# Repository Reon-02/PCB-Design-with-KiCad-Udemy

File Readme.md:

# PCB Design with KiCad — Udemy Course

<p align="center">
  A collection of PCB designs completed while following the
  <strong>PCB Design with KiCad - Updated for KiCad 9</strong> Udemy course.
</p>

---

## About

This repository contains the PCB designs, schematics, BOMs, manufacturing files, and supporting documentation created while completing the course.

The projects were developed as part of my practical learning process to gain hands-on experience with **schematic capture, component selection, PCB layout, routing, design verification, and preparation of PCB manufacturing files**.

The repository contains projects ranging from a simple LED circuit to power supply designs and a microcontroller-based data logger.

---

## Course

### PCB Design with KiCad - Updated for KiCad 9

**Platform:** Udemy

[View Course](https://www.udemy.com/share/105YR03@hdEVWNpVydDwXK-DHMVmjIG6j6jP2o1doZVhvYaCLZwN9b4QRBgg-SJO-xgzQPG_Kw==/)

---

## Projects

| No. | Project | Description |
|:---:|---|---|
| 01 | [LED Torch](./01_LED_Torch/) | Compact LED torch PCB |
| 02 | [Breadboard Power Supply](./02_Breadboard_Power_Supply/) | 5 V / 3.3 V regulated power supply |
| 03 | [Solar Power Supply](./03_Solar_Power_Supply/) | Solar-powered boost converter PCB |
| 04 | [MCU Data Logger](./04_MCU_Datalogger/) | ATmega328P-based data logger PCB |
---

## Skills Practiced

### PCB Design

- Schematic Capture
- Component Selection
- Footprint Assignment
- PCB Layout
- PCB Routing
- Ground Plane Creation
- Design Rule Checking (DRC)

### Manufacturing & Documentation

- Interactive BOM Generation
- Datasheet Reference
- Gerber Generation
- Gerber Verification
- PCB 3D Visualization
- Manufacturing File Preparation

### Version Control

- Git
- GitHub
- Repository Organization

---

## Tools Used

---

## Repository Structure

```text
PCB Design with KiCad-Udemy/
│
├── README.md
│
├── 01_LED_Torch/
│   ├── README.md
│   ├── KiCad/
│   ├── BOM/
│   ├── Gerbers/
│   └── Images/
│
├── 02_Breadboard_Power_Supply/
│   ├── README.md
│   ├── BOM/
│   ├── Datasheets/
│   ├── Gerbers/
│   ├── Images/
│   └── KiCad/
│
├── 03_Solar_Power_Supply/
│   ├── README.md
│   ├── BOM/
│   ├── Datasheets/
│   ├── Gerbers/
│   └── Images/
│
└── 04_MCU_Datalogger/
    ├── README.md
    ├── BOM/
    ├── Datasheets/
    ├── Gerbers/
    ├── Images/
    ├── Kicad_2layer/
    └── Kicad_4layer/

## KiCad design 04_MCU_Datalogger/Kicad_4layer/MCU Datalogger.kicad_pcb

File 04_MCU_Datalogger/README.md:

# MCU Data Logger

A microcontroller-based data logger PCB designed using KiCad as part of the **PCB Design with KiCad - Updated for KiCad 9** Udemy course.

The project is built around an **ATmega328P-AU** microcontroller and includes an external real-time clock, EEPROM memory, communication interfaces, programming interface, and external I/O connections. Both **2-layer and 4-layer PCB versions** were designed.

---

## Features

- ATmega328P-AU microcontroller
- DS1337S real-time clock
- External EEPROM memory
- I²C communication
- UART interface
- ISP programming interface
- 2-layer and 4-layer PCB versions
- Interactive HTML BOM
- Gerber generation and verification

---

## Working

The ATmega328P-AU acts as the main controller of the data logger. It communicates with the DS1337S real-time clock and external EEPROM through the I²C interface.

The real-time clock provides accurate time information, while the external EEPROM provides non-volatile memory for storing data.

The PCB also provides UART connectivity for serial communication and an ISP interface for programming the ATmega328P-AU. External connectors expose power, communication signals, and GPIO connections for interfacing with other circuits or modules.

The microcontroller operates using an external crystal oscillator, while the DS1337S uses a dedicated 32.768 kHz crystal for timekeeping.

---

## Schematic

The complete MCU Data Logger circuit was designed using KiCad.

---

## Layout Design

Two PCB implementations were developed for the project.

### 2-Layer PCB — Without Ground Zone

### 2-Layer PCB — With Ground Zone

### 4-Layer PCB — Without Ground Zone

### 4-Layer PCB — With Ground Zone

---

## 3D Visualization

### Front View

### Back View

---

## Components

| Reference | Component | Purpose |
|---|---|---|
| U4 | ATmega328P-AU | Main microcontroller |
| U3 | DS1337S | Real-time clock |
| U1, U2 | 24LC1025 | External EEPROM memory |
| Y1 | 32.768 kHz Crystal | RTC clock source |
| Y2 | 16 MHz Crystal | MCU clock source |
| D1 | LED | Power indication |
| J4 | ISP Connector | MCU programming |
| J1–J3 | External Connectors | Power, communication and I/O |
| H1–H4 | Mounting Holes | PCB mounting |

---

## Interactive BOM

The Interactive BOM provides component references, values, footprints, quantities, and interactive PCB component highlighting.

**[View Interactive BOM](https://reon-02.github.io/PCB-Design-with-KiCad-Udemy/04_MCU_Datalogger/BOM/MCU_Datalogger_ibom.html)**

---

## Design Verification

The PCB designs were checked using KiCad Design Rule Check (DRC), and the generated Gerber files were verified using the KiCad Gerber Viewer.

### 2-Layer Gerber Verification

### 4-Layer Gerber Verification

---

## Manufacturing Files

The project includes the generated Gerber and drill files required for PCB manufacturing.

The Gerber files include:

- Copper layers
- Solder mask layers
- Silkscreen layers
- Paste layers
- Edge cuts
- Drill files
- Gerber job file

---

## Datasheets

The relevant component datasheets used during the design are included in the `Datasheets` folder.

- [21941](./Datasheets/21941.pdf)
- [ATmega328P-AU Datasheet](./Datasheets/ATMEGA328PAU_Microchip_Technology.pdf)
- [DS1337S Datasheet](./Datasheets/DS1337S_Maxim_Integrated_Products.pdf)

---

## KiCad Project Files

The KiCad project files for both PCB versions are included in the repository:

- `Kicad_2layer/` — 2-layer PCB design
- `Kicad_4layer/` — 4-layer PCB design

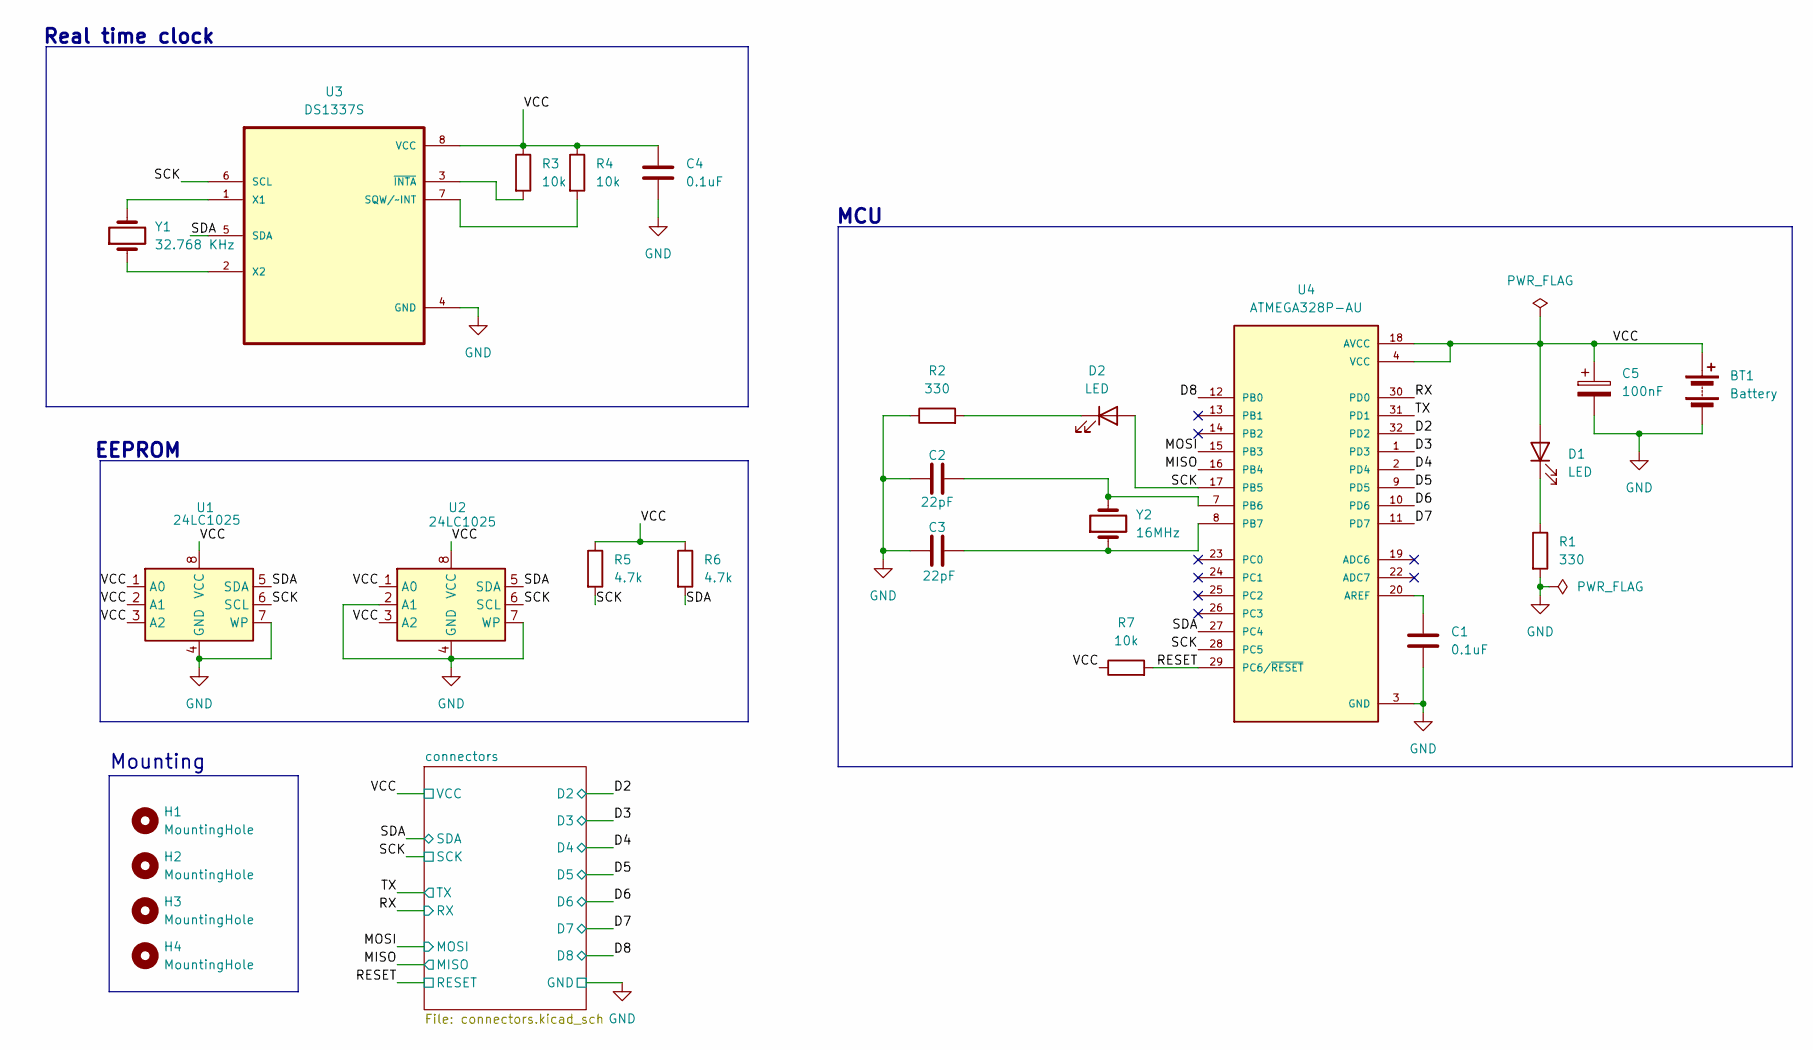
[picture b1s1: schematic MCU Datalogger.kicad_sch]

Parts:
BT1: Battery; PinHeader_1x02_P2.54mm_Vertical
C1, C4: 0.1uF; C_0805_2012Metric
C2, C3: 22pF; C_0805_2012Metric
C5: 100nF; C_0805_2012Metric
D1, D2: LED; LED_0805_2012Metric
H1, H2, H3, H4: MountingHole; MountingHole_2.1mm
R1, R2: 330; R_0805_2012Metric
R3, R4, R7: 10k; R_0805_2012Metric
R5, R6: 4.7k; R_0805_2012Metric
U1, U2: 24LC1025; SOIC-8_5.3x5.3mm_P1.27mm
U3: DS1337S; DS1337S+
U4: ATMEGA328P-AU; PARTREV 8271A
Y1: 32.768 KHz; Crystal_SMD_5032-2Pin_5.0x3.2mm_HandSoldering
Y2: 16MHz; Crystal_SMD_5032-2Pin_5.0x3.2mm_HandSoldering

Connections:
/D2: U4.32 (PD2); also elsewhere on the board
/D3: U4.1 (PD3); also elsewhere on the board
/D4: U4.2 (PD4); also elsewhere on the board
/D5: U4.9 (PD5); also elsewhere on the board
/D6: U4.10 (PD6); also elsewhere on the board
/D7: U4.11 (PD7); also elsewhere on the board
/D8: U4.12 (PB0); also elsewhere on the board
/MISO: U4.16 (PB4); also elsewhere on the board
/MOSI: U4.15 (PB3); also elsewhere on the board
/RESET: R7.2, U4.29 (PC6/~RESET); also elsewhere on the board
/RX: U4.30 (PD0); also elsewhere on the board
/SCK: D2.2 (A), R5.2, U1.6 (SCL), U2.6 (SCL), U3.6 (SCL), U4.17 (PB5), U4.28 (PC5); also elsewhere on the board
/SDA: R6.2, U1.5 (SDA), U2.5 (SDA), U3.5 (SDA), U4.27 (PC4); also elsewhere on the board
/TX: U4.31 (PD1); also elsewhere on the board
GND: BT1.2 (-), C1.1, C2.1, C3.1, C4.2, C5.2, R1.2, R2.1, U1.4 (GND), U1.7 (WP), U2.2 (A1), U2.4 (GND), U2.7 (WP), U3.4 (GND), U4.3 (GND), U4.5 (GND), U4.21 (GND); also elsewhere on the board
unnamed: D1.1 (K), R1.1
unnamed: D2.1 (K), R2.2
unnamed: R4.2, U3.7 (SQW/~INT)
unnamed: U3.1 (X1), Y1.2
unnamed: U3.2 (X2), Y1.1
unnamed: R3.2, U3.3 (~INTA)
unnamed: C1.2, U4.20 (AREF)
unnamed: C2.2, U4.7 (PB6), Y2.2
unnamed: C3.2, U4.8 (PB7), Y2.1
VCC: BT1.1 (+), C4.1, C5.1, D1.2 (A), R3.1, R4.1, R5.1, R6.1, R7.1, U1.1 (A0), U1.2 (A1), U1.3 (A2), U1.8 (VCC), U2.1 (A0), U2.3 (A2), U2.8 (VCC), U3.8 (VCC), U4.4 (VCC), U4.6 (VCC), U4.18 (AVCC); also elsewhere on the board

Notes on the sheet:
MCU
EEPROM
Mounting
Real time clock

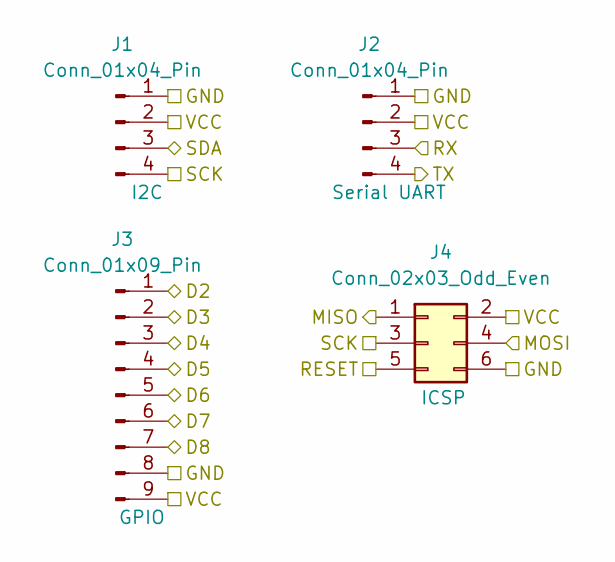
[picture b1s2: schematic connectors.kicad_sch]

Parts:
J1, J2: Conn_01x04_Pin; PinHeader_1x04_P2.54mm_Vertical
J3: Conn_01x09_Pin; PinHeader_1x09_P2.54mm_Vertical
J4: Conn_02x03_Odd_Even; PinHeader_2x03_P2.54mm_Vertical

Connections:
/D2: J3.1; also elsewhere on the board
/D3: J3.2; also elsewhere on the board
/D4: J3.3; also elsewhere on the board
/D5: J3.4; also elsewhere on the board
/D6: J3.5; also elsewhere on the board
/D7: J3.6; also elsewhere on the board
/D8: J3.7; also elsewhere on the board
/MISO: J4.1; also elsewhere on the board
/MOSI: J4.4; also elsewhere on the board
/RESET: J4.5; also elsewhere on the board
/RX: J2.3; also elsewhere on the board
/SCK: J1.4, J4.3; also elsewhere on the board
/SDA: J1.3; also elsewhere on the board
/TX: J2.4; also elsewhere on the board
GND: J1.1, J2.1, J3.8, J4.6; also elsewhere on the board
VCC: J1.2, J2.2, J3.9, J4.2; also elsewhere on the board

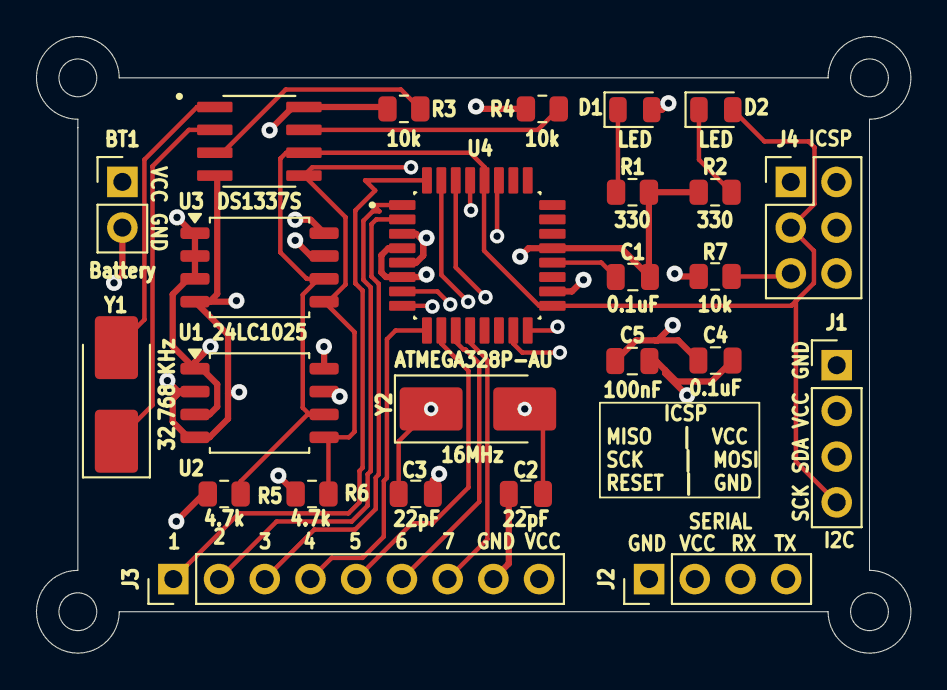
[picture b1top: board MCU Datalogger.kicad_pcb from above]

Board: 4 copper layers, 48.6 x 34.3 mm, 29 parts (0 on the bottom side), 25 nets.

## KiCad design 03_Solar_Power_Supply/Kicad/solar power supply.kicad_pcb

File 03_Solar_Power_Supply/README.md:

# Solar Power Supply

## Overview

This project is part of the **Solar Power Supply** section of the **PCB Design with KiCad - Updated for KiCad 9** Udemy course.

The circuit is designed to accept power from a solar source and provide a regulated output using a boost converter based on the **AP3015AKTR-G1**.

The design includes input protection, battery connection, power switching, boost conversion, filtering, and output voltage feedback.

---

## Features

- Solar power input
- Battery connection
- Reverse-polarity protection
- AP3015AKTR-G1 boost converter
- Inductor-based DC-DC conversion
- Output voltage feedback

---

## Working Principle

The solar power supply is designed to accept power from a solar source or battery and use a boost converter to generate the required output voltage.

### Solar Input

The solar input is connected through the input connector. An SS14 Schottky diode is used at the input to provide reverse-current protection and prevent current from flowing back toward the solar source.

### Battery and Power Switching

A battery can also be connected to the circuit. The solar and battery power paths are connected to the power switching section, where the 2N7002 MOSFET and associated resistors control the connection of the available input power to the boost converter.

### Boost Conversion

The AP3015AKTR-G1 boost converter performs the main DC-DC voltage conversion. The converter uses an external 10 µH inductor and switching circuitry to transfer energy from the input to the output and generate a higher voltage.

### Output Filtering

An SS14 Schottky diode is used in the boost converter output path. The output capacitors filter the converted voltage and reduce voltage ripple, providing a smoother DC output.

### Output Voltage Regulation

The output voltage is monitored using a resistor feedback network consisting of R1 and R2. The feedback voltage is applied to the FB pin of the AP3015, allowing the converter to adjust its switching operation and maintain the required output voltage.

---

## Schematic

The complete Solar Power Supply circuit was designed using KiCad.

---

## PCB Design

The PCB was designed using KiCad with the components arranged for a compact solar power supply circuit.

### PCB Layout

---

## 3D Visualization

### Front View

### Back View

---

## Components

| Reference | Component | Value / Part |
|---|---|---|
| U1 | Boost Converter | AP3015AKTR-G1 |
| Q1 | N-Channel MOSFET | 2N7002 |
| L1 | Inductor | 10 µH, 680 mA |
| D1 | Schottky Diode | SS14 |
| D2 | Schottky Diode | SS14 |
| R1 | Resistor | 1 MΩ |
| R2 | Resistor | 604 kΩ, 1% |
| R3 | Resistor | 10 kΩ |
| R4 | Resistor | 1 MΩ |
| C1 | Capacitor | 4.7 µF, 50 V, X7R |
| C2 | Capacitor | 22 µF, 10 V, X7R |
| C3 | Capacitor | 10 pF, 50 V, X7R |
| J2 | Connector | Battery Input |
| J4 | Connector | Solar Input |
| J3 | Connector | Power Switch |
| J1 | Connector | Output |

---

## Bill of Materials

An Interactive HTML BOM was generated using **InteractiveHtmlBom**.

[Open Interactive BOM](https://reon-02.github.io/PCB-Design-with-KiCad-Udemy/03_Solar_Power_Supply/BOM/Solar_Power_Supply_ibom.html)

The Interactive BOM provides:

- Component references
- Component values
- Footprints
- Component quantities
- Component locations
- Interactive PCB component highlighting

---

## Design Verification

### Design Rule Check

The PCB was checked using KiCad's **Design Rule Checker (DRC)**.

### Gerber Verification

The generated manufacturing files were opened and inspected using KiCad Gerber Viewer.

### Gerber Viewer with Ground Zone

---

## Manufacturing Files

The `Gerbers/` directory contains the manufacturing outputs generated from KiCad, including:

- Copper layers
- Solder mask layers
- Solder paste layers
- Silkscreen layers
- Board outline
- PTH drill file
- NPTH drill file
- Gerber job file

---

## Datasheets

Datasheets for the main components used in the design are included in the `Datasheets/` directory.

- [AP3015A Datasheet](./Datasheets/AP3015_A.pdf)
- [Abracon ASPI-0630LR-100M-T15 Datasheet](./Datasheets/ASPI-0630LR-100M-T15_Abracon.pdf)
- [2N7002A Datasheet](./Datasheets/NDS7002A-D.PDF)
- [SS14 Datasheet](./Datasheets/SS14_ON.pdf)

---

## KiCad Project Files

The complete KiCad project files are included in the project directory.

```text
solar power supply.kicad_pro
solar power supply.kicad_sch
solar power supply.kicad_pcb

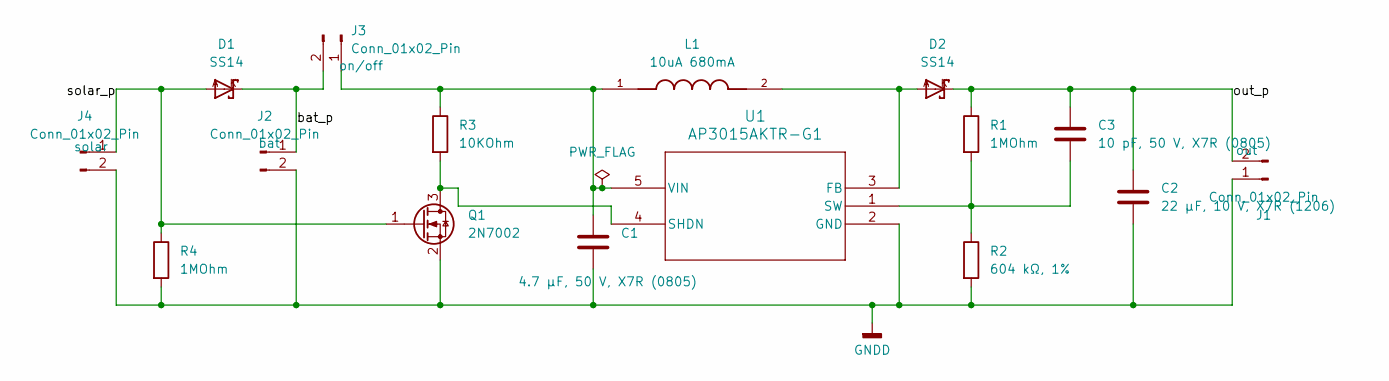
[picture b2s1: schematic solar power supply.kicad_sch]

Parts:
C1: 4.7 μF, 50 V, X7R (0805); C_0805_2012Metric
C2: 22 μF, 10 V, X7R (1206); C_1206_3216Metric
C3: 10 pF, 50 V, X7R (0805); C_0805_2012Metric
D1, D2: SS14
J1, J2, J4: Conn_01x02_Pin; PinHeader_1x02_P2.54mm_Horizontal
J3: Conn_01x02_Pin; SW_DIP_SPSTx01_Slide_9.78x4.72mm_W7.62mm_P2.54mm
L1: 10uA 680mA; IND_ASPI-0630LR-100M-T15; PARTREV B
Q1: 2N7002; SOT-23
R1, R4: 1MOhm; R_0805_2012Metric
R2: 604 kΩ, 1%; R_0805_2012Metric
R3: 10KOhm; R_0805_2012Metric
U1: AP3015AKTR-G1

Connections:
/bat_p: D1.K, J2.1, J3.2
/out_p: C2.1, C3.1, D2.K, J1.2, R1.1
/solar_p: D1.A, J4.1, Q1.1 (G), R4.1
GNDD: C1.2, C2.2, J1.1, J2.2, J4.2, Q1.2 (S), R2.2, R4.2, U1.2 (GND)
unnamed: C1.1, J3.1, L1.1, R3.1, U1.5 (VIN)
unnamed: Q1.3 (D), R3.2, U1.4 (SHDN)
unnamed: D2.A, L1.2, U1.3 (FB)
unnamed: C3.2, R1.2, R2.1, U1.1 (SW)

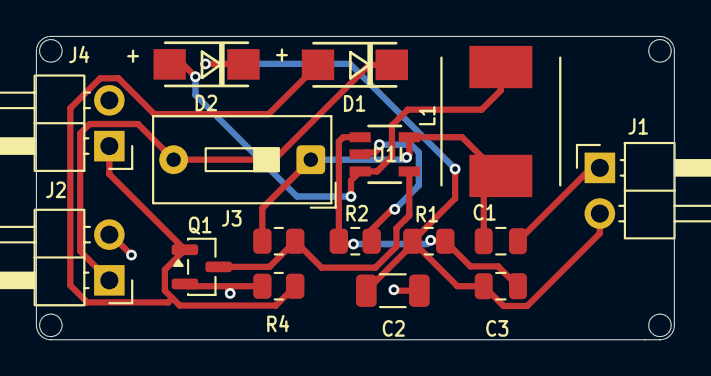
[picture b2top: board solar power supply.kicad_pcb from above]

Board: 2 copper layers, 35.4 x 16.8 mm, 16 parts (0 on the bottom side), 8 nets.

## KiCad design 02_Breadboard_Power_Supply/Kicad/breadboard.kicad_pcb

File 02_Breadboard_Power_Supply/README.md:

# Breadboard Power Supply

## Overview

This project is a breadboard power supply PCB designed as part of the **PCB Design with KiCad - Updated for KiCad 9** Udemy course.

The board accepts a **12 V DC input** and provides regulated **5 V and 3.3 V outputs** for powering breadboard-based electronic circuits.

The PCB includes voltage regulation, a power indicator LED, output selection, breadboard connectors, jumper-wire terminals, and a ground plane.

---

## Features

- 12 V DC input
- Regulated 5 V output using LM7805
- Regulated 3.3 V output using LM317
- Selectable output connectors
---
## Working Principle

The board accepts a 12 V DC input through the barrel jack. The input power is distributed to two voltage regulation sections to generate regulated 5 V and 3.3 V outputs.

### 12 V to 5 V Regulation

The 12 V input is supplied to the LM7805 voltage regulator through the power switch. The LM7805 regulates the input voltage to provide a stable 5 V output. Input and output capacitors are used for filtering and regulator stability.

### 12 V to 3.3 V Regulation

The 12 V input is also supplied to the LM317 adjustable voltage regulator. A resistor network connected to the adjustment circuit sets the regulator output to approximately 3.3 V.

### Power Indicator

An LED with a current-limiting resistor is used as a power indicator. The LED turns on when the board is powered.

### Output connections

The regulated 5 V and 3.3 V outputs are made available through dedicated connectors and screw terminals for connection to a breadboard or external circuit.

---

## Schematic

The complete circuit schematic was designed using KiCad.

---

## PCB Design

The PCB was designed as a compact through-hole board with the regulators, connectors, switch, and other components arranged for breadboard power supply use.

### PCB Layout

### PCB Layout with Ground Zone

---

## 3D Visualization

### Top View

### Alternate Top View

### Side View

### Back View

---

## Components

| Reference | Component | Value / Part |
|---|---|---|
| U1 | 5 V Voltage Regulator | LM7805_TO220 |
| U2 | Adjustable Voltage Regulator | LM317_TO220 |
| S1 | Power Switch | EG1218 |
| D1 | LED | Power Indicator |
| R1 | Resistor | 330 Ω |
| R2 | Resistor | 560 Ω |
| R3 | Resistor | 330 Ω |
| C1 | Capacitor | 10 µF |
| C2 | Capacitor | 0.1 µF |
| C3 | Capacitor | 1 µF |
| J6 | Barrel Jack | DC Power Input |
| J1, J3 | Output Connectors | Breadboard Output |
| J4, J7 | Screw Terminals | Jumper-Wire Output |

---

## Bill of Materials

An Interactive HTML BOM was generated using **InteractiveHtmlBom**.

[View Interactive BOM](https://reon-02.github.io/PCB-Design-with-KiCad-Udemy/02_Breadboard_Power_Supply/BOM/Breadboard_Power_Supply_ibom.html)

The interactive BOM provides:

- Component references
- Component values
- Footprints
- Descriptions
- Datasheet information where available
- Component quantities
- Component locations on the PCB

---

## Design Verification

### Design Rule Check

The PCB was checked using KiCad's Design Rule Checker (DRC).

### Gerber Verification

The generated manufacturing files were opened and inspected using KiCad Gerber Viewer.

### Gerber Viewer with Ground Zone

---

## Manufacturing Files

The `Gerbers/` directory contains the manufacturing outputs generated from KiCad, including:

- Front copper
- Back copper
- Front solder mask
- Back solder mask
- Front solder paste
- Back solder paste
- Front silkscreen
- Back silkscreen
- Board outline
- PTH drill file
- NPTH drill file
- Gerber job file

---

## Datasheets

Datasheets for the main components used in the design are included in the `Datasheets/` directory.

- [EG1218 Switch Datasheet](./Datasheets/EG1218.pdf)
- [LM317 Datasheet](./Datasheets/lm317.pdf)
- [MC7800 Datasheet](./Datasheets/MC7800-D.PDF)

---

## KiCad Project Files

The complete KiCad project files are available in the `KiCad/` directory.

```text
KiCad/
├── breadboard.kicad_pro
├── breadboard.kicad_sch
└── breadboard.kicad_pcb
```

---

## Project Structure

```text
02_Bread_Power_Supply/
│
├── README.md
│
├── KiCad/
│   ├── breadboard.kicad_pro
│   ├── breadboard.kicad_sch
│   └── breadboard.kicad_pcb
│
├── BOM/
│   └── Breadboard_Power_Supply_ibom.html
│
├── Datasheets/
│   ├── EG1218.pdf
│   ├── lm317.pdf
│   └── MC7800-D.PDF
│
├── Gerbers/
│   ├── Gerber files
│   └── Drill files
│
└── Images/
    ├── Schematic.png
    ├── PCB_Layout.png
    ├── PCB_layout_with_zone.png
    ├── 3d_top_view.png
    ├── 3d_top_view1.png
    ├── 3d_side.png
    ├── 3d_back.png
    ├── DRC.png
    ├── Gerber_Viewer.png
    └── Gerber_viewer_zone.png
```

---

## What I Practiced

Through this project, I practiced:

- Schematic capture
- Voltage regulator circuit design
- Component and footprint selection
- Through-hole PCB layout
- PCB routing and ground plane creation
- Design Rule Checking (DRC)
- Interactive BOM generation
- Gerber generation and verification
- Preparing PCB files for manufacturing
---

## Course

This project was completed as part of:

**[PCB Design with KiCad - Updated for KiCad 9](https://www.udemy.com/share/105YR03@hdEVWNpVydDwXK-DHMVmjIG6j6jP2o1doZVhvYaCLZwN9b4QRBgg-SJO-xgzQPG_Kw==/)**

**Platform:** Udemy

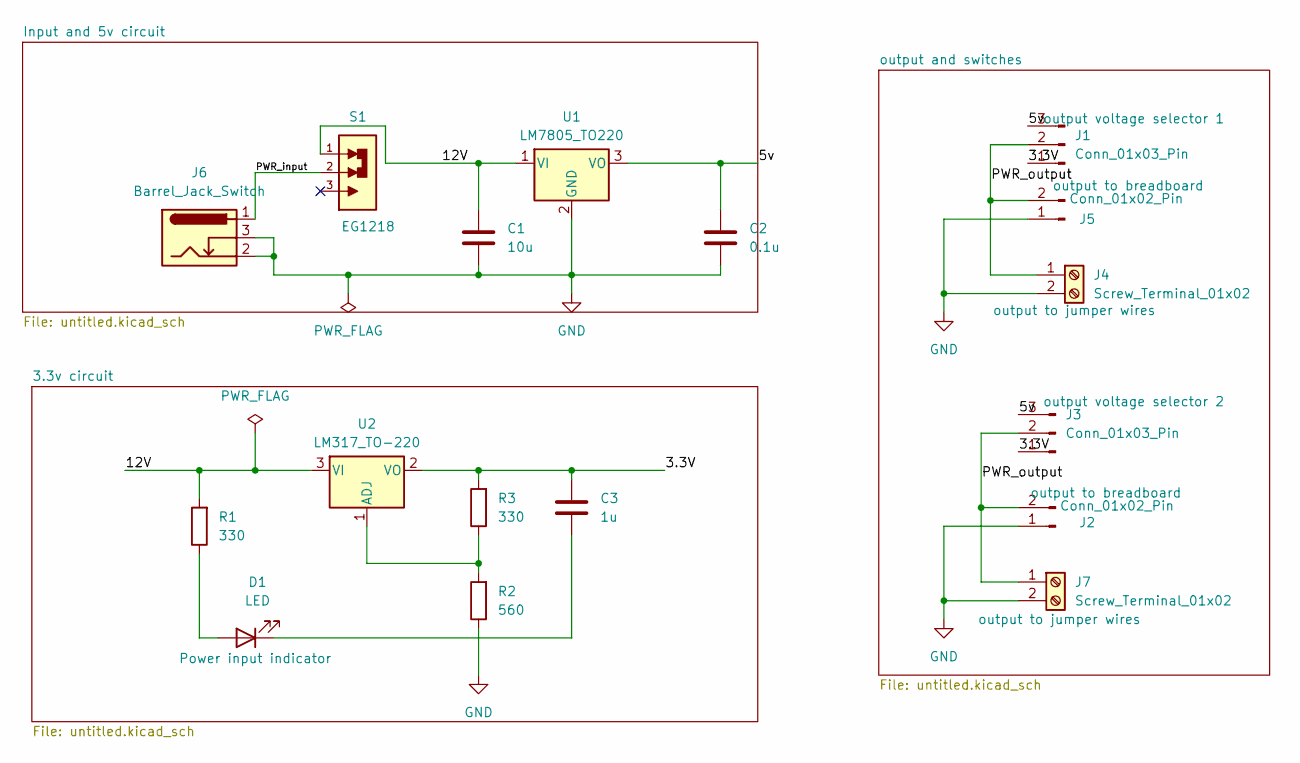
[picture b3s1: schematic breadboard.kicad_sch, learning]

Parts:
C1: 10u; C_Disc_D3.0mm_W1.6mm_P2.50mm
C2: 0.1u; C_Disc_D3.0mm_W1.6mm_P2.50mm
C3: 1u; C_Disc_D3.0mm_W1.6mm_P2.50mm
D1: LED; LED_D5.0mm
J1, J3: Conn_01x03_Pin; PinHeader_1x03_P2.54mm_Vertical
J2, J5: Conn_01x02_Pin; PinHeader_1x02_P2.54mm_Vertical
J4, J7: Screw_Terminal_01x02
J6: Barrel_Jack_Switch; BarrelJack_Horizontal
R1, R3: 330; R_Axial_DIN0204_L3.6mm_D1.6mm_P7.62mm_Horizontal
R2: 560; R_Axial_DIN0204_L3.6mm_D1.6mm_P7.62mm_Horizontal
S1: EG1218; SW_EG1218
U1: LM7805_TO220; TO-220-3_Vertical
U2: LM317_TO-220; TO-220-3_Vertical

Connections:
/3.3V: C3.1, J1.1, J3.1, R3.2, U2.2 (VO)
/5v: C2.1, J1.3, J3.3, U1.3 (VO)
/12V: C1.1, R1.2, S1.1, U1.1 (VI), U2.3 (VI)
/PWR_input: J6.1, S1.2
/PWR_output: J1.2, J2.2, J3.2, J4.1, J5.2, J7.1
GND: C1.2, C2.2, J2.1, J4.2, J5.1, J6.2, J6.3, J7.2, R2.1, U1.2 (GND)
unnamed: D1.2 (A), R1.1
unnamed: C3.2, D1.1 (K)
unnamed: R2.2, R3.1, U2.1 (ADJ)

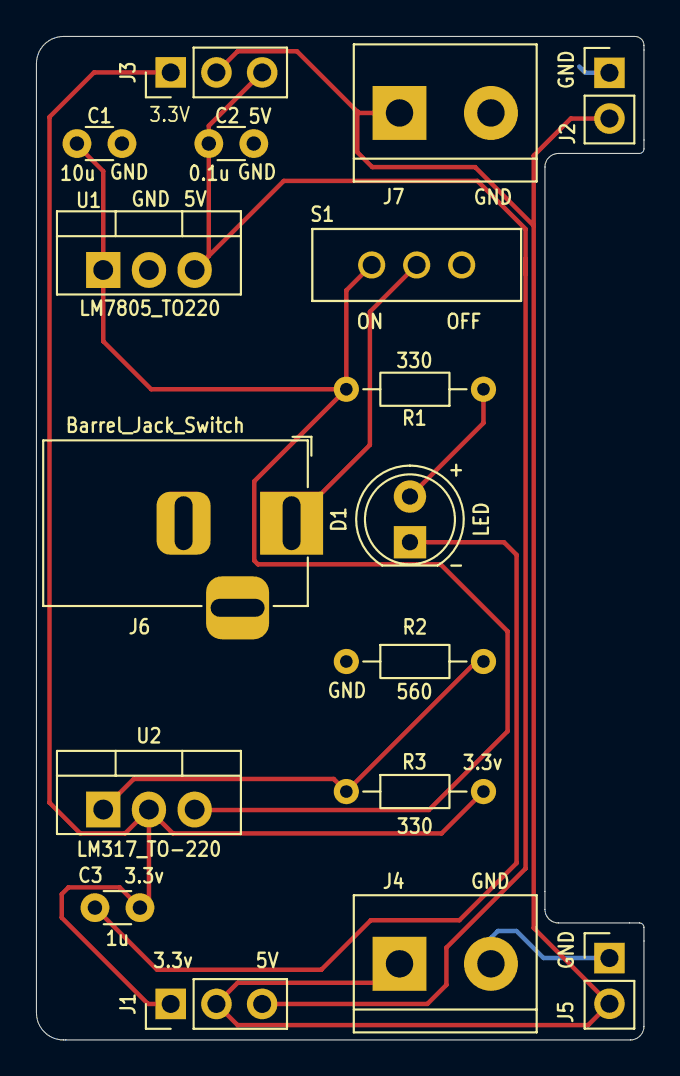
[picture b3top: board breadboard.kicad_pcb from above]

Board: 2 copper layers, 33.8 x 55.8 mm, 17 parts (0 on the bottom side), 9 nets.

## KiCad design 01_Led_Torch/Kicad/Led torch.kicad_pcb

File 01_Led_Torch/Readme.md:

# LED Torch

## Overview

This project is a compact LED torch PCB designed as part of the **PCB Design with KiCad - Updated for KiCad 9** Udemy course.

The circuit uses a single battery cell to power an LED through a current-limiting resistor and an SPST switch.

This project was recreated in KiCad as part of my practical PCB design learning process.

---

## Circuit

The basic circuit consists of:

- Single-cell battery
- SPST ON/OFF switch
- 1 kΩ current-limiting resistor
- 5 mm LED

### Schematic

---

## PCB Design

The PCB was designed as a compact torch-shaped board with an integrated battery holder footprint.

### PCB Layout

### 3D View

#### Front

#### Back

---

## Components

| Reference | Component | Value | Footprint |
|---|---|---|---|
| R1 | Resistor | 1 kΩ | R_Axial_DIN0204_L3.6mm_D1.6mm_P7.62mm_Horizontal |
| D1 | LED | LED | LED_D5.0mm |
| SW1 | SPST Switch | SW_SPST | SW_TH_Tactile_Omron_B3F-100x |
| BT1 | Battery Holder | Battery Cell | BatteryHolder_Keystone_1058_1x2032 |

---

## Bill of Materials

The Interactive HTML BOM was generated using the **InteractiveHtmlBom** tool.

**[View Interactive BOM](./BOM/LED_Torch_ibom.html)**

The interactive BOM provides:

- Component references
- Component values
- Footprints
- Descriptions
- Quantities
- Component locations on the PCB

---

## Design Verification

### Design Rule Check

The PCB was checked using KiCad's Design Rule Checker (DRC).

### Gerber Verification

The generated manufacturing files were opened and inspected using KiCad Gerber Viewer.

---

## Manufacturing Files

The `Gerbers/` directory contains the manufacturing outputs generated from KiCad, including:

- Front copper
- Back copper
- Front solder mask
- Back solder mask
- Front silkscreen
- Back silkscreen
- Board outline
- Drill files
- Gerber job file

---

## KiCad Project Files

The complete KiCad project files are available in the `KiCad/` directory.

```text
KiCad/
├── Led torch.kicad_pro
├── Led torch.kicad_sch
└── Led torch.kicad_pcb

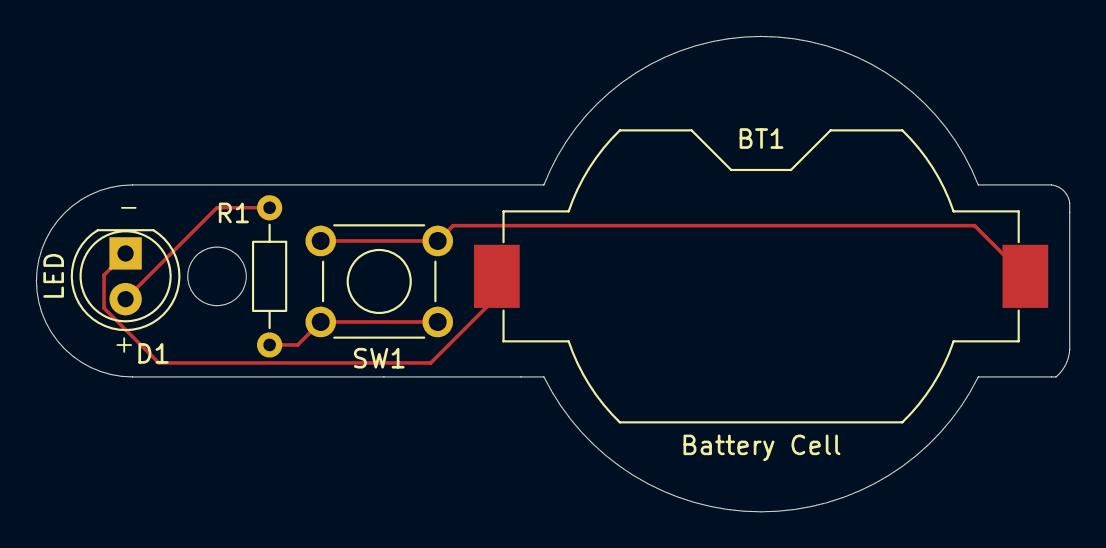
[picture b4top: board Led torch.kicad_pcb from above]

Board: 2 copper layers, 57.4 x 26.4 mm, 4 parts (0 on the bottom side), 4 nets.

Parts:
BT1: Battery Cell; BatteryHolder_Keystone_1058_1x2032
D1: LED; LED_D5.0mm
R1: 1k; R_Axial_DIN0204_L3.6mm_D1.6mm_P7.62mm_Horizontal
SW1: SW_SPST; SW_TH_Tactile_Omron_B3F-100x

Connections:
/LED_Cathode: BT1.2 (-), D1.1 (K)
/bat_pos: BT1.1 (+), SW1.2 (B)
unnamed: D1.2 (A), R1.1
unnamed: R1.2, SW1.1 (A)
